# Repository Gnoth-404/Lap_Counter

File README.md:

# Lap_Counter
Time Counter for VGU Line Follower Robot

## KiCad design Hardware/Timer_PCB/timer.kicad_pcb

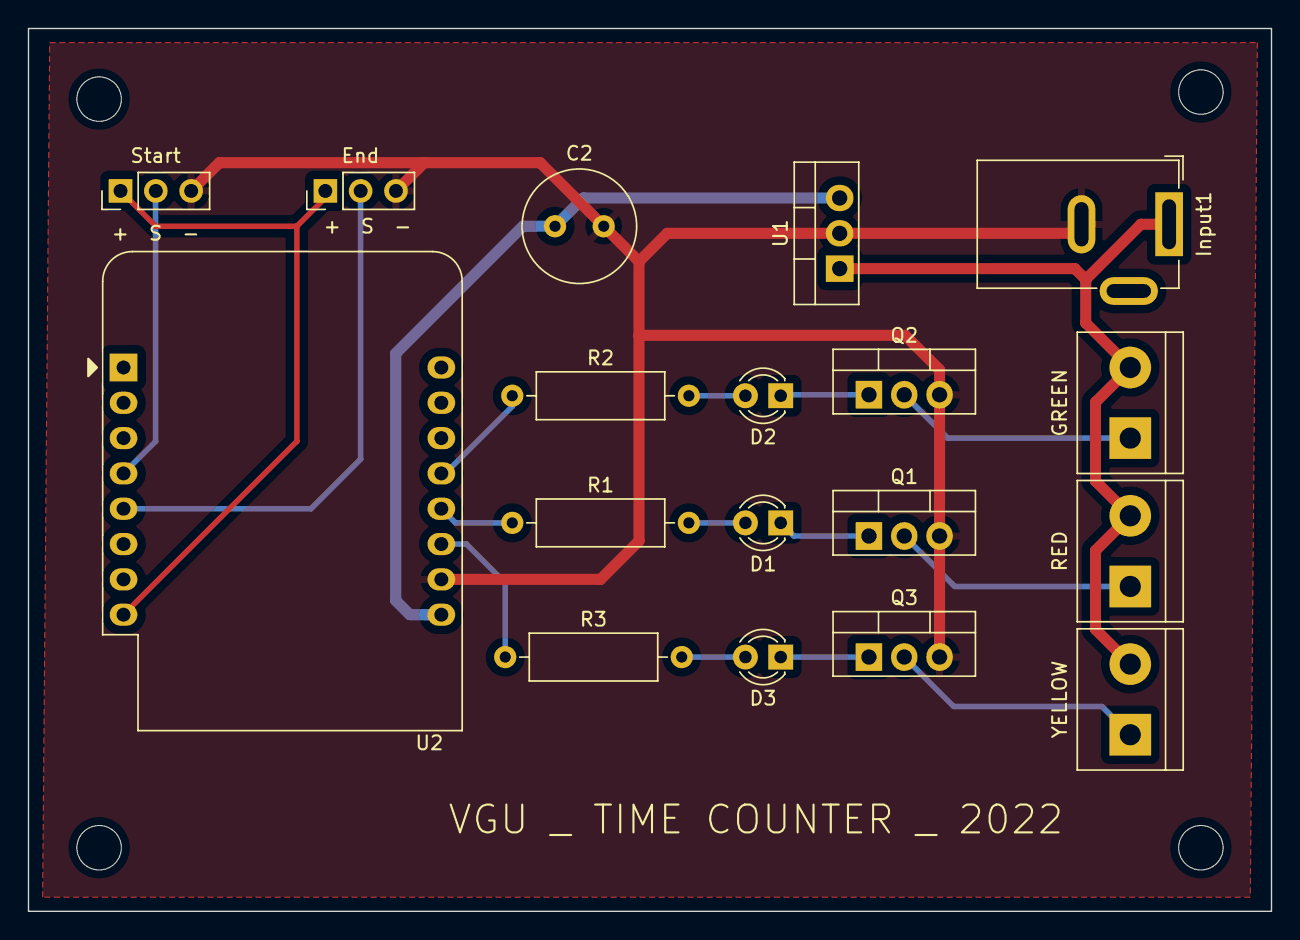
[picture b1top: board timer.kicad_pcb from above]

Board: 2 copper layers, 89.4 x 63.5 mm, 18 parts (0 on the bottom side), 18 nets.

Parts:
C2: 10uF; C_Radial_D8.0mm_H7.0mm_P3.50mm
D1, D2, D3: LED; LED_D3.0mm
GREEN: GREEN; TerminalBlock_bornier-2_P5.08mm
Input1: 12V Input; BarrelJack_GCT_DCJ200-10-A_Horizontal
J1: Start; PinHeader_1x03_P2.54mm_Vertical
J2: End; PinHeader_1x03_P2.54mm_Vertical
Q1, Q2, Q3: TIP120; TO-220-3_Vertical
R1, R2, R3: 2.2k; R_Axial_DIN0309_L9.0mm_D3.2mm_P12.70mm_Horizontal
RED: RED; TerminalBlock_bornier-2_P5.08mm
U1: LM7805_TO220; TO-220-3_Vertical
U2: WeMos_D1_mini; WEMOS_D1_mini_light
YELLOW: YELLOW; TerminalBlock_bornier-2_P5.08mm

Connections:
+3V3: J1.1, J2.1, U2.8 (3V3)
+5V: C2.1, U1.3 (VO), U2.9 (5V)
/GREEN: R1.1, U2.12 (D3)
/L1: Q1.2 (C), RED.1 (-)
/L2: GREEN.1 (-), Q2.2 (C)
/L3: Q3.2 (C), YELLOW.1 (-)
/RED: R2.1, U2.13 (SDA/D2)
/Start: J1.2, U2.4 (SCK/D5)
/Stop: J2.2, U2.5 (MISO/D6)
/Vin: GREEN.2 (+), Input1.1, RED.2 (+), U1.1 (VI), YELLOW.2 (+)
/YELLOW: R3.1, U2.11 (D4)
GND: C2.2, Input1.2, J1.3, J2.3, Q1.3 (E), Q2.3 (E), Q3.3 (E), U1.2 (GND), U2.10 (GND)
unnamed: D1.1 (K), Q1.1 (B)
unnamed: D1.2 (A), R1.2
unnamed: D2.1 (K), Q2.1 (B)
unnamed: D2.2 (A), R2.2
unnamed: D3.1 (K), Q3.1 (B)
unnamed: D3.2 (A), R3.2

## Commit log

2022-09-24 Update PCB and Firmware
